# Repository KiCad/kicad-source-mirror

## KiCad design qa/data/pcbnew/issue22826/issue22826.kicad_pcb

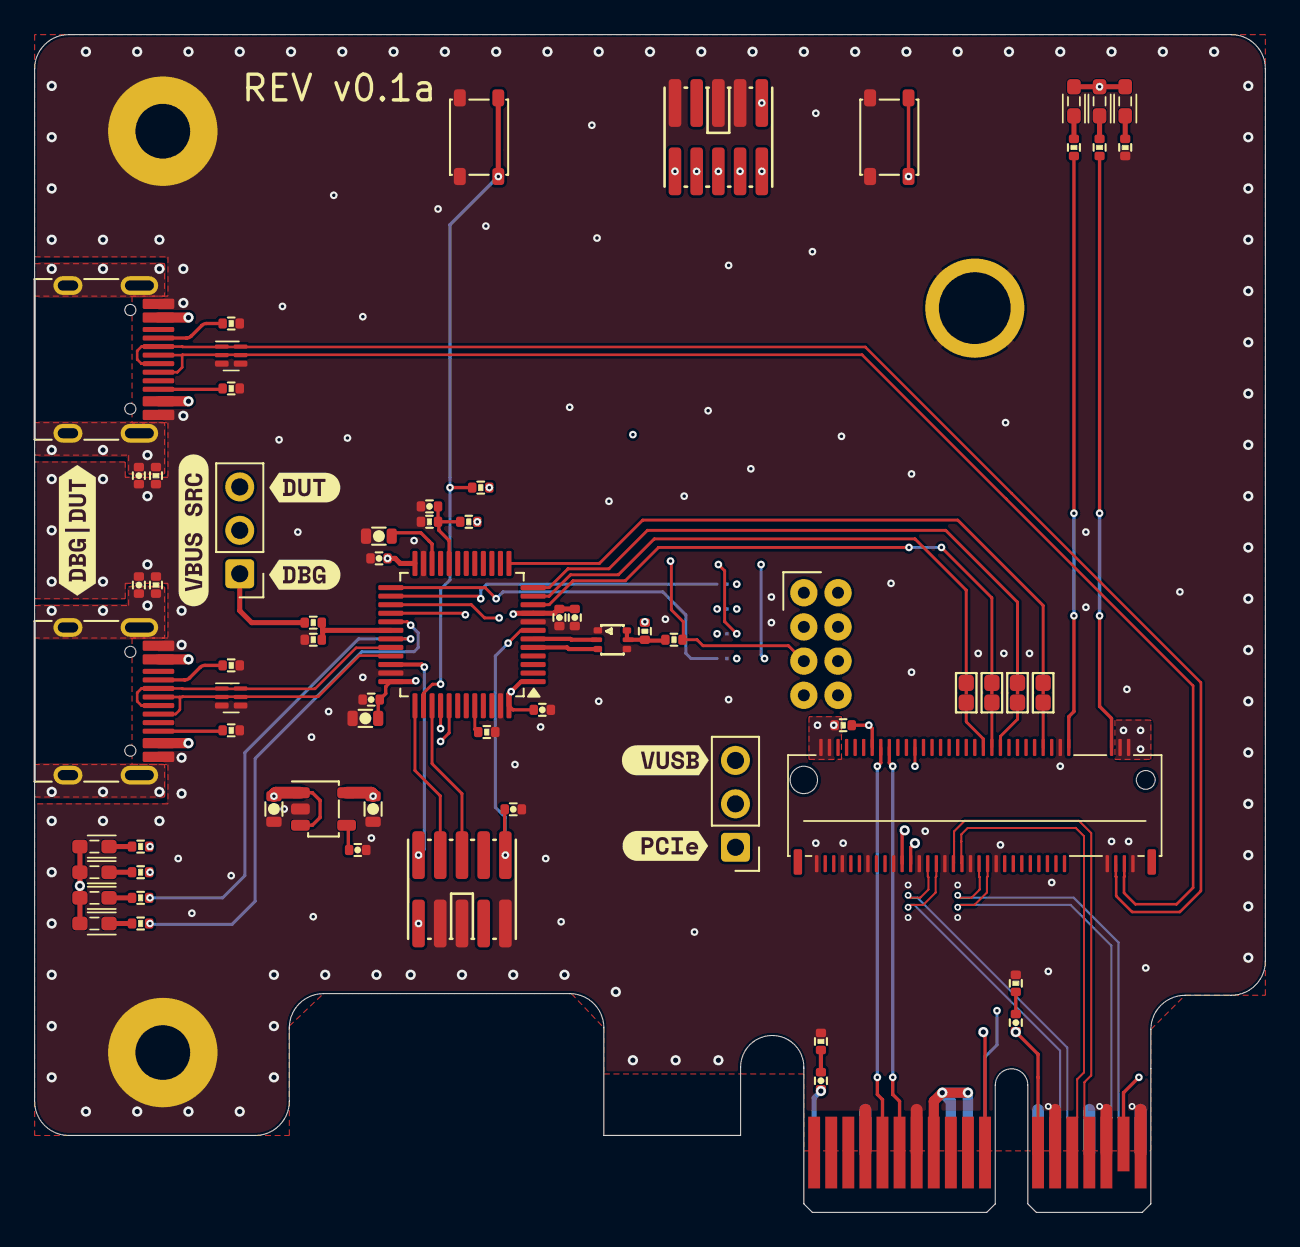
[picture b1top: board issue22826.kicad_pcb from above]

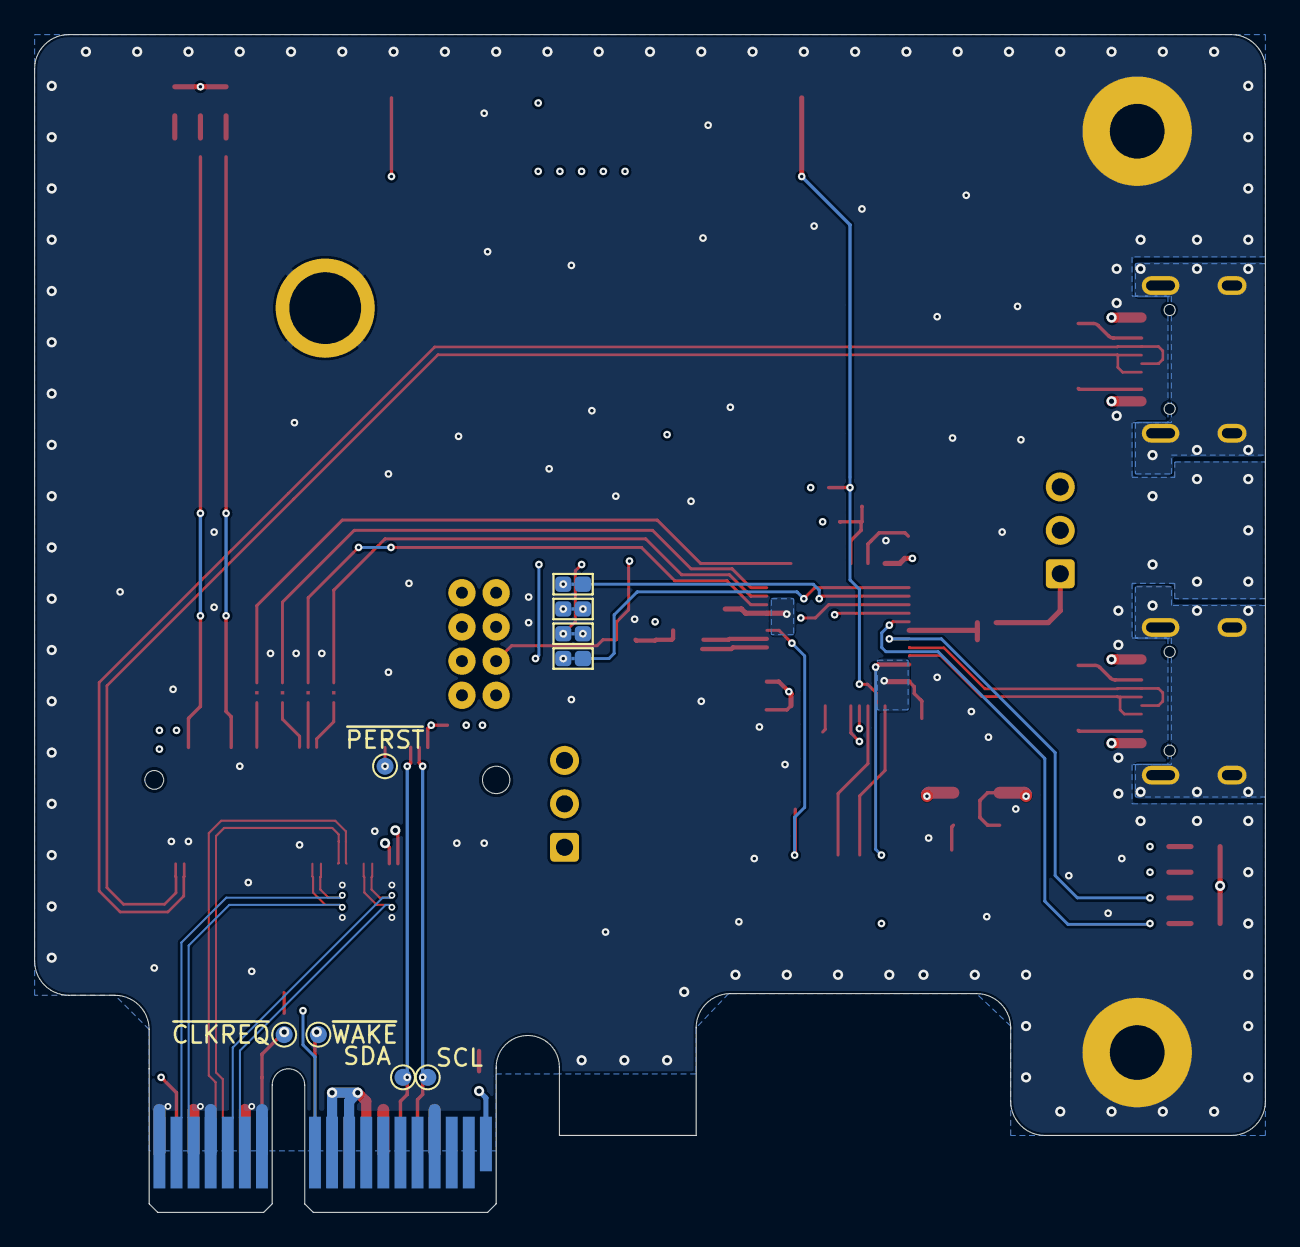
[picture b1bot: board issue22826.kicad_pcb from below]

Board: 6 copper layers, 72.0 x 68.9 mm, 85 parts (9 on the bottom side), 75 nets.

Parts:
C1, C2, C10, C11, C12, C13, C14, C15: 100n; C_0402
C3: 10n; C_0402
C4, C5, C9: 4u7; C_0603
C7, C8: 1p; C_0402
C16: 10u; C_0603
C17: 1u; C_0402
D1: YELLOW; LED0603
D2: ORANGE; LED0603
D3: RED; LED0603
D4, D5, D6, D7: GREEN; LED0603
H1: MountingHole_Pad; M2_MountingPost
H2, H3: MountingHole_Pad; MountingHole_3.2mm_M3_Pad
J1: PCIe-x1; PCIe-x1-Edge
J2: DUT; USB_C_Receptacle_HRO_TYPE-C-31-M-12
J3: DBG; USB_C_Receptacle_HRO_TYPE-C-31-M-12
J4: NGFF_Module_A+E; APCI0162-P001A
J5: DBG; 838-22-008-10-001101
J6, J7: JTAG; FTSH-105-XX-X-DV
JP1: VBUS_SRC; PinHeader_1x03_P2.54mm_Vertical
JP2, JP3, JP4, JP5, JP6, JP7, JP8, JP9: Jumper_2_Bridged; J_NC_0603_20
JP10: M2_3v3; PinHeader_1x03_P2.54mm_Vertical
Q3: DMG1024UV-7; SOT-666
R1, R2, R4, R5: 5k1; R_0402
R3, R6: 1M; R_0402
R7, R8: 42.5; R_0402
R9, R10, R11, R14, R16, R24: 10k; R_0402
R12, R13: 4k7; R_0402
R15: 100; R_0402
R17, R18, R19, R20, R21, R22, R23: 330; R_0402
SW1: SW_Push; SW_SPST_3x4x2.5
SW2: ALERT; SW_SPST_3x4x2.5
TP1: SCL; TestPoint_Pad_D1.0mm
TP2: SDA; TestPoint_Pad_D1.0mm
TP3: ~{PERST}; TestPoint_Pad_D1.0mm
TP4: ~{CLKREQ}; TestPoint_Pad_D1.0mm
TP5: ~{WAKE}; TestPoint_Pad_D1.0mm
U1, U2: SP3400-02UTG; UDFN-6L
U3: VREG_3v3; SOT-23-5
U4: STM32U575CITx; LQFP-48_7x7mm_P0.5mm
kibuzzard-68DC7BCF: G***; kibuzzard-68DC7BCF
kibuzzard-68DC7C1C: G***; kibuzzard-68DC7C1C
kibuzzard-68DC7C24: G***; kibuzzard-68DC7C24
kibuzzard-68DC7D29: G***; kibuzzard-68DC7D29
kibuzzard-693E0E83: G***; kibuzzard-693E0E83
kibuzzard-693E0EAD: G***; kibuzzard-693E0EAD

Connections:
+3V3_PCIe: J1.A9 (3V3), J1.A10 (3V3), J1.B8 (3V3), JP10.1 (A)
+3V3_USB: C5.1, C11.1, C12.1, C13.1, C15.1, C16.1, C17.1, D1.2 (A), D2.2 (A), D3.2 (A), D4.2 (A), J6.1, JP10.3 (B), R10.1, U3.5 (OUT), U4.1 (VBAT), U4.9 (VDDA), U4.24 (VDD), U4.36 (VDD), U4.48 (VDD)
+M2_3v3: D5.2 (A), D6.2 (A), D7.2 (A), J4.2 (+3V3), J4.4 (+3V3), J4.72 (+3V3), J4.74 (+3V3), J7.1, JP10.2 (C), R13.1, R16.1, R24.1
/BMP_CTS: JP6.1 (A), U4.10 (USART2_CTS)
/BMP_RTS: JP7.1 (A), U4.11 (USART2_RTS)
/BMP_RX: JP9.1 (A), U4.13 (USART2_RX)
/BMP_TCK: JP3.2 (B), U4.26 (PB13)
/BMP_TDI: JP5.2 (B), U4.28 (PB15)
/BMP_TDO: JP4.2 (B), U4.27 (PB14)
/BMP_TMS: JP2.2 (B), U4.25 (PB12)
/BMP_TX: JP8.1 (A), U4.12 (USART2_TX)
/D0+: J2.A6 (D+), J2.B6 (D+), J4.3 (USB_D+), U1.2 (IO2), U1.5 (NC)
/D0-: J2.A7 (D-), J2.B7 (D-), J4.5 (USB_D-), U1.1 (IO1), U1.6 (NC)
/D1+: J3.A6 (D+), J3.B6 (D+), U2.2 (IO2), U2.5 (NC), U4.33 (USB_OTG_FS_DP)
/D1-: J3.A7 (D-), J3.B7 (D-), U2.1 (IO1), U2.6 (NC), U4.32 (USB_OTG_FS_DM)
/DBG_PWR: C10.1, R13.2, R14.1, U4.20 (PB2)
/M2_CTS: J4.34 (NC/UART_RTS), JP6.2 (B)
/M2_RTS: J4.36 (NC/UART_CTS), JP7.2 (B)
/M2_RX: J4.32 (NC/UART_RXD), JP8.2 (B)
/M2_TX: J4.22 (NC/UART_TXD), JP9.2 (B)
/REFCLK+: J1.A13 (REFCLK+), J4.47 (REFCLKp0)
/REFCLK-: J1.A14 (REFCLK-), J4.49 (REFCLKn0)
/RX0+: J1.A16 (RX0+), J4.35 (PERp0)
/RX0-: J1.A17 (RX0-), J4.37 (PERn0)
/SCL: J1.B5 (SMCLK), J4.60 (I2C_CLK), TP1.1 (1_1)
/SDA: J1.B6 (SMDAT), J4.58 (I2C_DATA), TP2.1 (1_1)
/SHIELD0: C1.2, J2.S1 (SHIELD), R3.1
/SHIELD1: C2.2, J3.S1 (SHIELD), R6.1
/SWDCLK: J6.4, U4.37 (DEBUG_JTCK-SWCLK)
/SWDIO: J6.2, U4.34 (DEBUG_JTMS-SWDIO)
/SWO: J6.6, U4.39 (DEBUG_JTDO-SWO)
/TCK: J5.2, J7.4, JP3.1 (A)
/TDI: J5.4, J7.8, JP5.1 (A)
/TDO: J5.6, J7.6, JP4.1 (A)
/TMS: J5.8, J7.2, JP2.1 (A)
/TX0+: J1.B14 (TX0+), J4.41 (PETp0)
/TX0-: J1.B15 (TX0-), J4.43 (PETn0)
/VBUS: C4.1, JP1.2 (C), U3.1 (IN), U3.3 (EN)
/VBUS_DET: R11.1, R12.2, U4.30 (USB_OTG_FS_VBUS)
/iRST: Q3.2 (G), U4.6 (PH1)
/iRST_SNS: Q3.3 (D), U4.5 (PH0)
/~CLKREQ: C7.1, J1.B12 (CLKRQ#), J4.53 (~CLKREQ0), TP4.1 (1_1)
/~LED0: R17.2, U4.40 (TIM3_CH1)
/~LED1: R18.2, U4.41 (TIM3_CH2)
/~LED2: R19.2, U4.31 (TIM1_CH3)
/~LED3: R20.2, U4.29 (TIM1_CH1)
/~M2_LED0: J4.6 (~LED1), R21.2
/~M2_LED1: J4.16 (~LED2), R22.2
/~PERST: J1.A11 (PERST#), J4.52 (~PERST0), TP3.1 (1_1)
/~PROGRAM: J5.5, J7.10, R15.2
/~PRSNT: C8.1, J1.A1 (PRSNT1#), J1.B17 (PRSNT2#)
/~RST: C14.1, J6.10, U4.7 (NRST)
/~WAKE: J1.B11 (WAKE#), J4.55 (~PEWAKE0), TP5.1 (1_1)
GND: C1.1, C2.1, C3.2, C4.2, C5.2, C9.2, C10.2, C11.2, C12.2, C13.2, C14.2, C15.2, C16.2, C17.2, H1.1 (1_1), H2.1 (1_1), H3.1 (1_1), J1.A4 (GND), J1.A12 (GND), J1.A15 (GND), J1.A18 (GND), J1.B4 (GND), J1.B7 (GND), J1.B13 (GND), J1.B16 (GND), J1.B18 (GND), J2.A1 (GND), J2.A12 (GND), J2.B1 (GND), J2.B12 (GND), J3.A1 (GND), J3.A12 (GND), J3.B1 (GND), J3.B12 (GND), J4.1 (GND), J4.7 (GND), J4.18 (GND), J4.33 (GND), J4.39 (GND), J4.45 (GND), J4.51 (GND), J4.57 (GND), J4.63 (GND), J4.69 (GND), J4.75 (GND), J6.3, J6.5, J6.9, J7.3, J7.5, J7.9, Q3.1 (S), Q3.4 (S), R1.2, R2.1, R3.2, R4.2, R5.1, R6.2, R7.2, R8.2, R9.2, R11.2, R14.2, R23.2, SW1.2, SW2.1, U1.3 (GND), U1.4 (GND), U2.3 (GND), U2.4 (GND), U3.2 (GND), U4.8 (VSSA), U4.23 (VSS), U4.35 (VSS), U4.47 (VSS)
unnamed: C7.2, R7.1
unnamed: C8.2, R8.1
unnamed: D1.1 (K), R17.1
unnamed: D2.1 (K), R18.1
unnamed: D3.1 (K), R19.1
unnamed: D4.1 (K), R20.1
unnamed: D5.1 (K), R21.1
unnamed: D6.1 (K), R22.1
unnamed: D7.1 (K), R23.1
unnamed: J2.A5 (CC1), R1.1
unnamed: J2.B5 (CC2), R2.2
unnamed: J3.A5 (CC1), R4.1
unnamed: J3.B5 (CC2), R5.2
unnamed: J4.62 (~ALERT), R24.2, SW2.2
unnamed: Q3.5 (G), Q3.6 (D), R15.1, R16.2
unnamed: C3.1, U3.4 (BYP)
unnamed: R10.2, SW1.1, U4.38 (PA15)
unnamed: R9.1, U4.44 (PH3)
unnamed: C9.1, U4.22 (VCAP)
VBUS_DBG: J3.A4 (VBUS), J3.A9 (VBUS), J3.B4 (VBUS), J3.B9 (VBUS), JP1.1 (A), R12.1
VBUS_DUT: J2.A4 (VBUS), J2.A9 (VBUS), J2.B4 (VBUS), J2.B9 (VBUS), JP1.3 (B)
